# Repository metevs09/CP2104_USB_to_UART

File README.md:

# CP2104 USB to UART Converter
This repository contains design files, schematics, and documentation for a CP2104-based USB to UART converter. The converter leverages the Silicon Labs CP2104 chip to bridge USB communication with UART, making it ideal for interfacing microcontrollers and other serial devices with a PC.

## Overview
The CP2104 USB to UART Converter is designed to provide a reliable and cost-effective solution for serial communication over USB. This project includes:

- Hardware Schematics: Detailed circuit diagrams for the converter.
- PCB Design Files: All necessary files for fabricating the printed circuit board (PCB).
- Documentation: Assembly instructions, component details, and usage guidelines.
  
## Features

- USB to UART Bridging: Seamlessly converts USB signals to UART for serial communication.
- Plug and Play: Designed for easy integration with microcontrollers and other UART-enabled devices.
- Compact and Efficient: Optimized for a small form factor and reliable operation.
- Comprehensive Documentation: Includes schematics, PCB layouts, and step-by-step assembly instructions.
  
## Repository Structure
```
CP2104_USB_to_UART/
├── schematics/       # Circuit schematics for the converter
├── pcb/              # PCB design files (Gerber files, layouts, etc.)
├── docs/             # Documentation and assembly instructions

```
## Prerequisites

- CP210x Drivers: Ensure that you have the latest CP210x drivers installed on your computer. You can download them from the Silicon Labs website.
- PCB Fabrication: Access to a PCB manufacturing service if you plan to build the hardware.
- Basic Electronics Knowledge: Familiarity with reading schematics and assembling electronic circuits.
  
Getting Started

1. Clone the Repository:
```
git clone https://github.com/metevs09/CP2104_USB_to_UART.git
```
2. Review the Schematics:

- Open the files in the schematics/ folder using your preferred schematic editor.
  
3. PCB Fabrication:

- Use the design files in the pcb/ folder to order your PCB.

4. Assembly:
- Follow the detailed instructions in the docs/ folder for component placement and soldering.
  
5. Driver Installation:

- Install the CP210x drivers on your computer to enable proper USB-to-UART communication.

## Usage
Once the hardware is assembled:

- Connect: Plug the USB connector into your computer.
- Communicate: The converter will be recognized as a virtual COM port. Use any terminal program (e.g., PuTTY, Tera Term) to interface with your UART device.
- Test: Verify communication by sending and receiving serial data through the converter.
> Note: Always observe proper safety precautions when assembling and testing electronic circuits.

License
This project is licensed under the MIT License. See the LICENSE file for more details.

Acknowledgements
Special thanks to Silicon Labs for the CP2104 chip.
Thanks to the open-source community for their valuable resources and contributions.

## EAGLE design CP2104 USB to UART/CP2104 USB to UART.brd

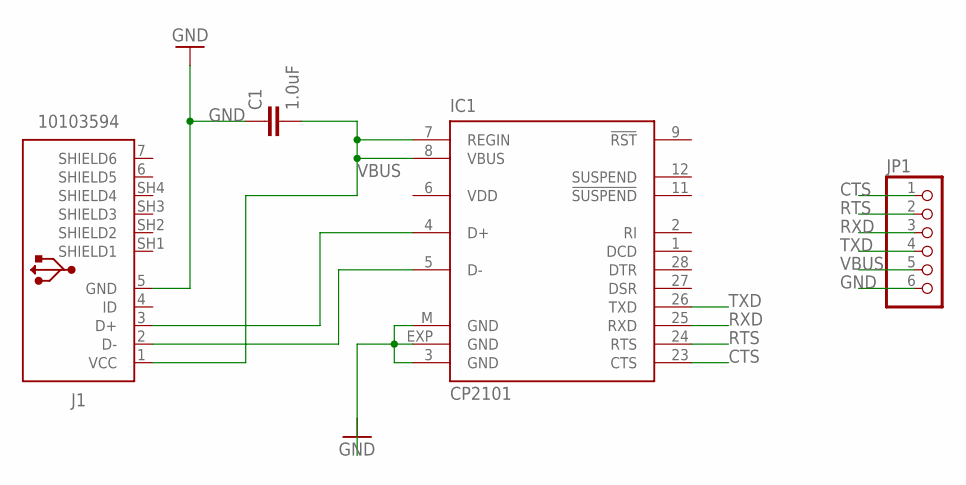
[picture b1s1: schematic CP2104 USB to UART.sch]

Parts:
C1: 1.0uF; 0805
IC1: CP2101; MLP28
J1: 10103594
JP1: PINHD-1X6; 1X06

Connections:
CTS: IC1.23 (CTS), JP1.1
GND: C1.1, IC1.3 (GND), IC1.EXP (GND), IC1.M (GND), J1.5 (GND), JP1.6
unnamed: IC1.4 (D+), J1.3 (D+)
unnamed: IC1.5 (D-), J1.2 (D-)
RTS: IC1.24 (RTS), JP1.2
RXD: IC1.25 (RXD), JP1.3
TXD: IC1.26 (TXD), JP1.4
VBUS: C1.2, IC1.7 (REGIN), IC1.8 (VBUS), J1.1 (VCC), JP1.5
VDD: IC1.6 (VDD)

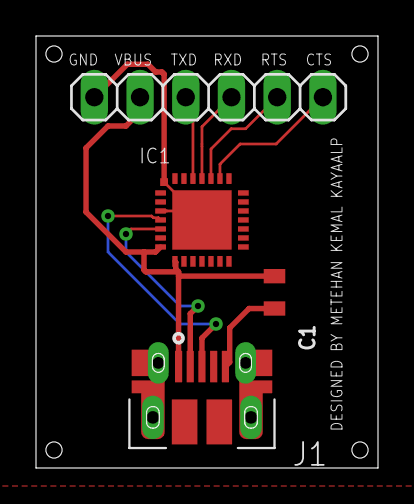
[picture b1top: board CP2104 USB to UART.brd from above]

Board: 2 copper layers, 19.0 x 24.0 mm, 4 parts (0 on the bottom side), 8 nets.

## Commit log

2025-02-20 Update README.md
    Edited README file
2025-02-20 Update README.md
    Added Picture to README

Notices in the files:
parts and their libraries:
SparkFun-Capacitors: Licensing: Creative Commons ShareAlike 4.0 International - https://creativecommons.org/licenses/by-sa/4.0
